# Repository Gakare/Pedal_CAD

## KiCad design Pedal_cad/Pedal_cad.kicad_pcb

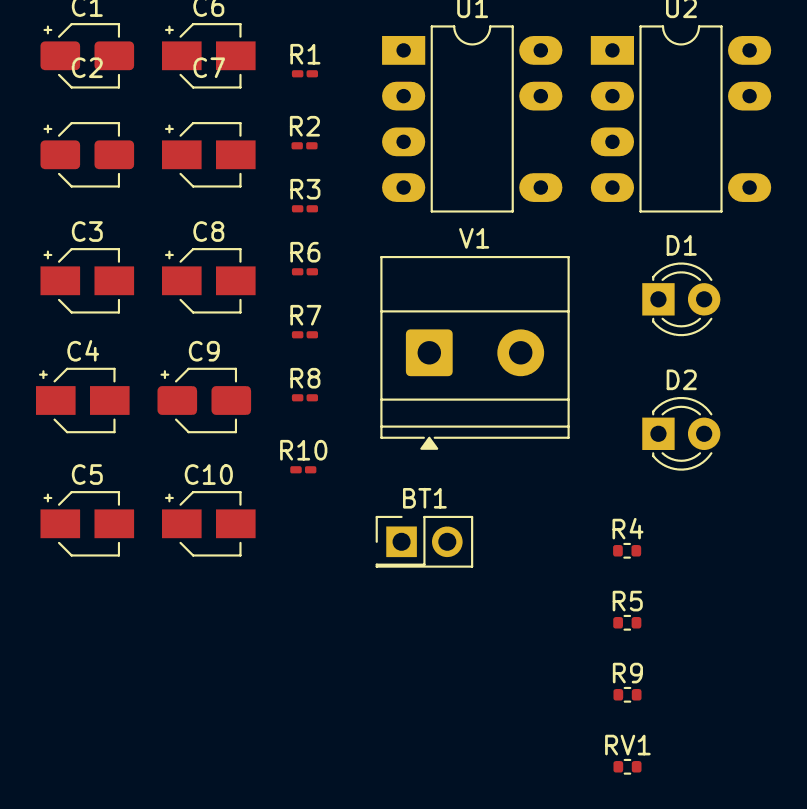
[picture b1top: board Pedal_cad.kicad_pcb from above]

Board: 2 copper layers, 27 parts (0 on the bottom side), 14 nets, no tracks yet.

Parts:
BT1: 9V; PinHeader_2x01_P2.54mm_Vertical
C1, C2: 47 uF; CP_Elec_3x5.4
C3, C8: 100 pF; CP_Elec_3x5.3
C4, C10: 22 nF; CP_Elec_3x5.3
C5: 47 nF; CP_Elec_3x5.3
C6: 50 pF; CP_Elec_3x5.3
C7: 680 nF; CP_Elec_3x5.3
C9: 1 uF; CP_Elec_3x5.4
D1, D2: RED; LED_D3.0mm
R1, R2, R3, R8: 10k; R_0201_0603Metric_Pad0.64x0.40mm_HandSolder
R4, R5: 1M; R_0402_1005Metric
R6: 4.7k; R_0201_0603Metric_Pad0.64x0.40mm_HandSolder
R7: 2.2k; R_0201_0603Metric_Pad0.64x0.40mm_HandSolder
R9: 680k; R_0402_1005Metric
R10: 1k; R_0201_0603Metric_Pad0.64x0.40mm_HandSolder
RV1: 100k; R_0402_1005Metric
U1, U2: PowerIntegrations_PDIP-8B
V1: VSIN; TerminalBlock_Phoenix_MKDS-1,5-2-5.08_1x02_P5.08mm_Horizont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

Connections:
/9V: BT1.1 (+), C1.1, R1.1, U1.3 (V+), U2.3 (V+)
/Output: C10.1, D1.2 (A), D2.1 (K), R10.2
/Pot_Ref: C6.2, R7.2, RV1.1, RV1.2, U1.5
/Vref: C2.1, R1.2, R2.1, R5.1, U2.1 (+)
GND: BT1.2 (-), C1.2, C2.2, C3.2, C5.2, C10.2, D1.1 (K), D2.2 (A), R2.2, R4.2, U1.4 (V-), U2.4 (V-), V1.2
unnamed: C3.1, C4.1, R3.2, R4.1
unnamed: C5.1, R6.2
unnamed: C7.2, R8.1
unnamed: C8.2, C9.1, R9.2, U2.5
unnamed: C9.2, R10.1
unnamed: R3.1, V1.1
unnamed: C4.2, R5.2, U1.1 (+)
unnamed: C6.1, R6.1, R7.1, U1.2 (-)
unnamed: C8.1, R8.2, R9.1, U2.2 (-)
